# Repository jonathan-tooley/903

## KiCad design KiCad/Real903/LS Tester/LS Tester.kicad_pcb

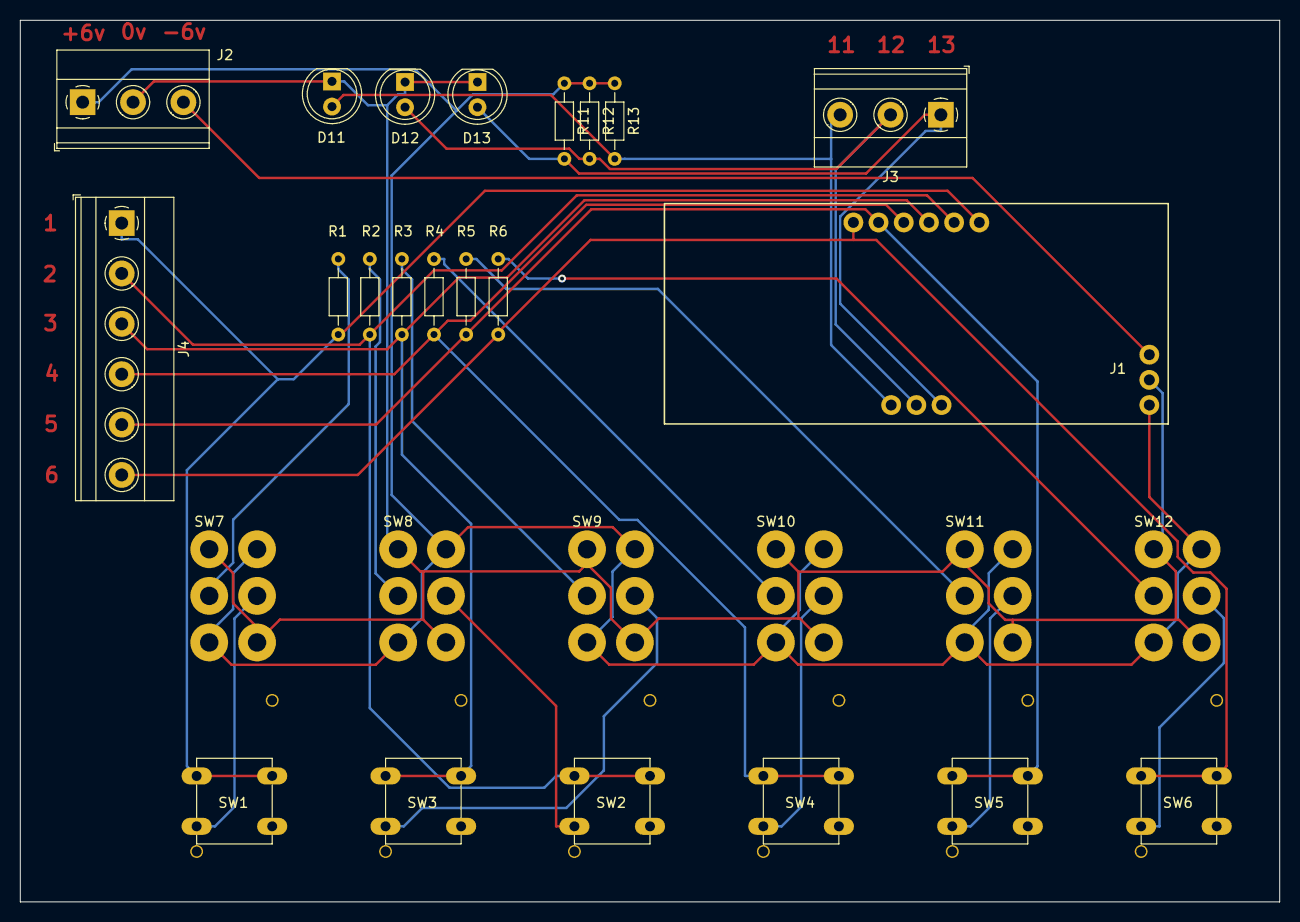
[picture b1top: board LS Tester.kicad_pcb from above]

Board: 2 copper layers, 127.0 x 88.9 mm, 28 parts (0 on the bottom side), 24 nets.

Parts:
D11, D12, D13: LED_D5.0mm
J1: LSAConnect; LSA
J2, J3: Conn_01x03; TerminalBlock_Phoenix_MKDS-1,5-3-5.08_1x03_P5.08mm_Horizont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
J4: TerminalBlock_Phoenix_MKDS-1,5-6-5.08_1x06_P5.08mm_Horizont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
R1, R2, R3, R4, R5, R6: 1k; R_Axial_DIN0204_L3.6mm_D1.6mm_P7.62mm_Horizontal
R11, R12, R13: 2k2; R_Axial_DIN0204_L3.6mm_D1.6mm_P7.62mm_Horizontal
SW1, SW2, SW3, SW4, SW5, SW6: SW_KEYSW
SW7, SW8, SW9, SW10, SW11, SW12: DPDT

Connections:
0v: D11.1, D12.1, D13.1, J1.22, J2.2, SW7.1, SW7.6, SW8.1, SW8.6, SW9.1, SW9.6, SW10.1, SW10.6, SW11.1, SW11.6, SW12.1, SW12.6
1: J1.1, J4.1, R1.1, SW1.0
2: J1.2, J4.2, R2.1, SW2.0
3: J1.3, J4.3, R3.1, SW3.0
4: J1.4, J4.4, R4.1, SW4.0
5: J1.5, J4.5, R5.1, SW5.0
6: J1.6, J4.6, R6.1, SW6.0
11: D13.2, J1.11, J3.1, R11.2
12: D12.2, J1.12, J3.2, R12.2
13: D11.2, J1.13, J3.3, R13.2
+6v: J1.21, J2.1, R11.1, R12.1, R13.1, SW7.3, SW7.4, SW8.3, SW8.4, SW9.3, SW9.4, SW10.3, SW10.4, SW11.3, SW11.4, SW12.3, SW12.4
unnamed: J1.23, J2.3
unnamed: R1.2, SW7.2
unnamed: R2.2, SW8.2
unnamed: R3.2, SW9.2
unnamed: R4.2, SW10.2
unnamed: R5.2, SW11.2
unnamed: R6.2, SW12.2
unnamed: SW1.1, SW7.5
unnamed: SW2.1, SW8.5
unnamed: SW3.1, SW9.5
unnamed: SW4.1, SW10.5
unnamed: SW5.1, SW11.5
unnamed: SW6.1, SW12.5

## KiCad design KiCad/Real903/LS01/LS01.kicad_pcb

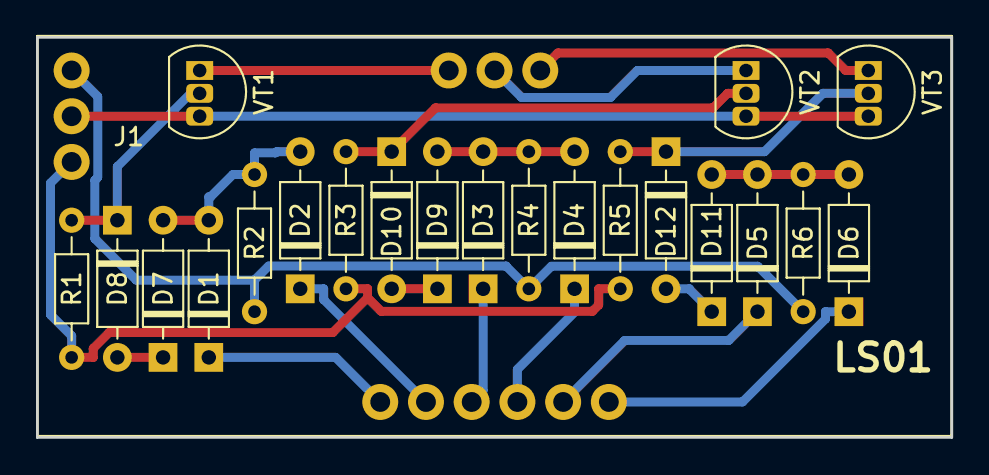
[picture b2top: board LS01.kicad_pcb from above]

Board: 2 copper layers, 50.8 x 22.2 mm, 22 parts (0 on the bottom side), 21 nets.

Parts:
D1, D2, D3, D4, D5, D6, D7, D8, D9, D10, D11, D12: 1N4148; D_DO-35_SOD27_P7.62mm_Horizontal
J1: LSAConnect; LSA
R1, R3, R5: 22k; R_Axial_DIN0204_L3.6mm_D1.6mm_P7.62mm_Horizontal
R2, R4, R6: 2.2k; R_Axial_DIN0204_L3.6mm_D1.6mm_P7.62mm_Horizontal
VT1, VT2, VT3: BC548; TO-92L_Inline

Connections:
0v: J1.22, VT1.3, VT2.3, VT3.3
1: D1.1, J1.1
2: D2.1, J1.2
3: D3.1, J1.3
4: D4.1, J1.4
5: D5.1, J1.5
6: D6.1, J1.6
11: J1.11, VT1.1
12: J1.12, VT2.1
13: J1.13, VT3.1
+6v: J1.21, R2.1, R4.1, R6.1
-6v: J1.23, R1.2, R3.2, R5.2
unnamed: D1.2, D2.2, D7.2, R2.2
unnamed: D3.2, D4.2, D9.2, R4.2
unnamed: D7.1, D8.2
unnamed: D8.1, R1.1, VT1.2
unnamed: D10.1, R3.1, VT2.2
unnamed: D9.1, D10.2
unnamed: D11.1, D12.2
unnamed: D5.2, D6.2, D11.2, R6.2
unnamed: D12.1, R5.1, VT3.2

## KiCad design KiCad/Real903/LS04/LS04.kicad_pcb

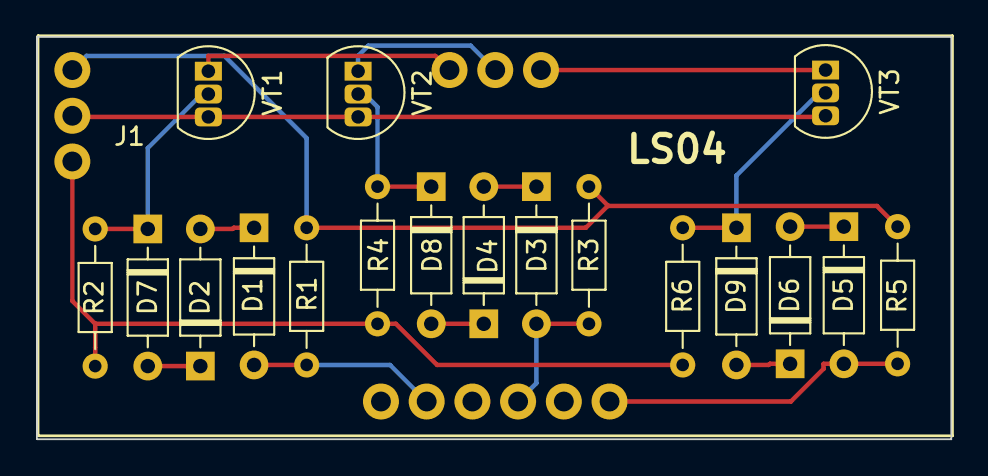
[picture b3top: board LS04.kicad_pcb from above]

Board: 2 copper layers, 50.8 x 22.4 mm, 19 parts (0 on the bottom side), 18 nets.

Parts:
D1, D2, D3, D4, D5, D6, D7, D8, D9: 1N4148; D_DO-35_SOD27_P7.62mm_Horizontal
J1: LSAConnect; LSA
R1, R3, R5: 3k9; R_Axial_DIN0204_L3.6mm_D1.6mm_P7.62mm_Horizontal
R2, R4, R6: 22k; R_Axial_DIN0204_L3.6mm_D1.6mm_P7.62mm_Horizontal
VT1, VT2, VT3: BC548; TO-92L_Inline

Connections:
0v: J1.22, VT1.1, VT2.1, VT3.1
2: D1.2, J1.2, R1.2
4: D3.2, J1.4, R3.2
6: D5.2, J1.6, R5.2
11: J1.11, VT1.3
12: J1.12, VT2.3
13: J1.13, VT3.3
+6v: J1.21, R1.1, R3.1, R5.1
-6v: J1.23, R2.2, R4.2, R6.2
unnamed: D1.1, D2.2
unnamed: D2.1, D7.2
unnamed: D3.1, D4.2
unnamed: D4.1, D8.2
unnamed: D5.1, D6.2
unnamed: D6.1, D9.2
unnamed: D7.1, R2.1, VT1.2
unnamed: D8.1, R4.1, VT2.2
unnamed: D9.1, R6.1, VT3.2

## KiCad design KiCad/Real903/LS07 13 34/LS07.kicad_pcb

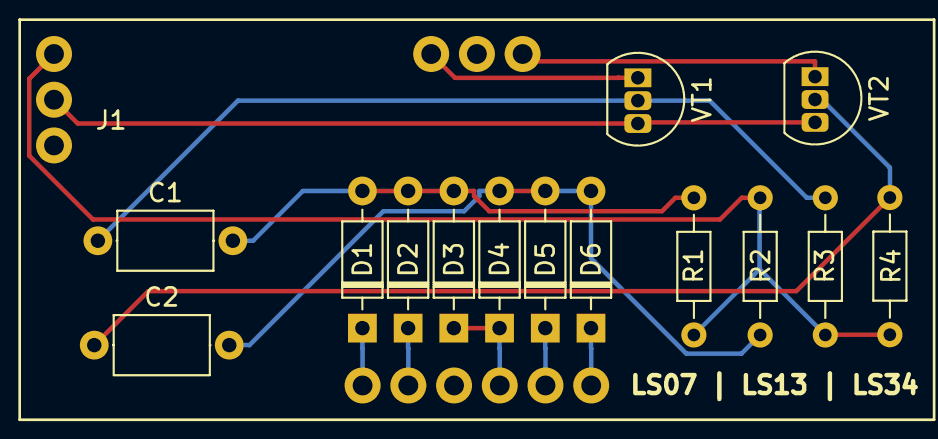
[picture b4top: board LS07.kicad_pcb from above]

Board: 2 copper layers, 15 parts (0 on the bottom side), 13 nets.

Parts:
C1, C2: C; C_Axial_L5.1mm_D3.1mm_P7.50mm_Horizontal
D1, D2, D3, D4, D5, D6: 1N4148; D_DO-35_SOD27_P7.62mm_Horizontal
J1: LSAConnect; LSA
R1, R2: 820; R_Axial_DIN0204_L3.6mm_D1.6mm_P7.62mm_Horizontal
R3, R4: 2k7; R_Axial_DIN0204_L3.6mm_D1.6mm_P7.62mm_Horizontal
VT1, VT2: BC548; TO-92L_Inline

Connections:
0v: J1.22, VT1.1, VT2.1
1: D1.1, J1.1
2: D2.1, J1.2
4: D3.1, D4.1, J1.4
5: D5.1, J1.5
6: D6.1, J1.6
11: J1.11, VT1.3
13: J1.13, VT2.3
+6v: J1.21, R1.1, R2.2, R3.1, R4.2
unnamed: C1.1, R3.2, VT1.2
unnamed: C1.2, D1.2, D2.2, D3.2, R1.2
unnamed: C2.1, R4.1, VT2.2
unnamed: C2.2, D4.2, D5.2, D6.2, R2.1
